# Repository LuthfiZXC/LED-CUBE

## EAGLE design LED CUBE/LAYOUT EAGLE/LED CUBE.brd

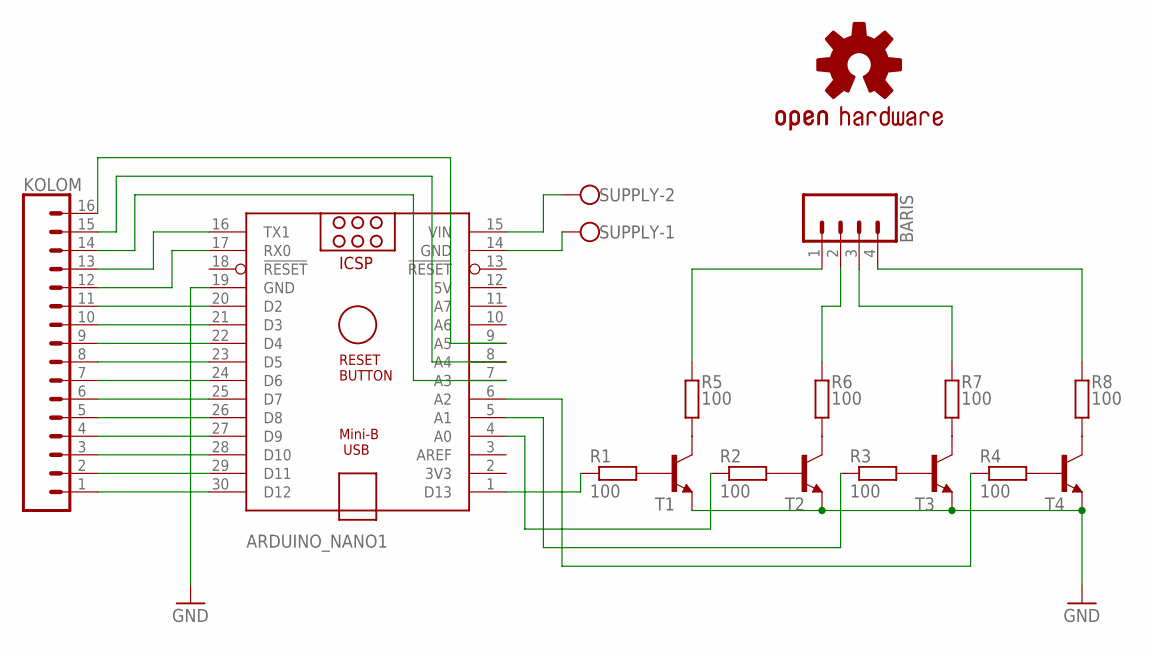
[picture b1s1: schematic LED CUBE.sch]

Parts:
ARDUINO_NANO1: ARDUINO_NANO
BARIS: CONN_04LONGPADS; 1X04_LONGPADS
KOLOM: CONN_16LONGPADS; 1X16_LONGPADS
LOGO2: OSHW-LOGOL-COPPER; OSHW-LOGO-L_COPPER
R1, R2, R3, R4: 100; 0411/15
R5, R6, R7, R8: 100; 0309/10
SUPPLY: W237-102
T1, T2, T3, T4: -NPN-TO92-EBC; TO92-EBC

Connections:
5V: ARDUINO_NANO1.12 (5V)
GND: ARDUINO_NANO1.19 (GND), T1.E, T2.E, T3.E, T4.E
unnamed: ARDUINO_NANO1.30 (D12), KOLOM.1
unnamed: ARDUINO_NANO1.29 (D11), KOLOM.2
unnamed: ARDUINO_NANO1.28 (D10), KOLOM.3
unnamed: ARDUINO_NANO1.27 (D9), KOLOM.4
unnamed: ARDUINO_NANO1.26 (D8), KOLOM.5
unnamed: ARDUINO_NANO1.25 (D7), KOLOM.6
unnamed: ARDUINO_NANO1.24 (D6), KOLOM.7
unnamed: ARDUINO_NANO1.23 (D5), KOLOM.8
unnamed: ARDUINO_NANO1.22 (D4), KOLOM.9
unnamed: ARDUINO_NANO1.21 (D3), KOLOM.10
unnamed: ARDUINO_NANO1.20 (D2), KOLOM.11
unnamed: ARDUINO_NANO1.17 (RX0), KOLOM.12
unnamed: ARDUINO_NANO1.16 (TX1), KOLOM.13
unnamed: ARDUINO_NANO1.7 (A3), KOLOM.14
unnamed: ARDUINO_NANO1.14 (GND), SUPPLY.1
unnamed: ARDUINO_NANO1.8 (A4), KOLOM.15
unnamed: ARDUINO_NANO1.9 (A5), KOLOM.16
unnamed: R1.2, T1.B
unnamed: R2.2, T2.B
unnamed: R3.2, T3.B
unnamed: R4.2, T4.B
unnamed: ARDUINO_NANO1.1 (D13), R1.1
unnamed: ARDUINO_NANO1.4 (A0), R2.1
unnamed: ARDUINO_NANO1.5 (A1), R3.1
unnamed: ARDUINO_NANO1.6 (A2), R4.1
unnamed: R5.1, T1.C
unnamed: R6.1, T2.C
unnamed: R7.1, T3.C
unnamed: R8.1, T4.C
unnamed: BARIS.1, R5.2
unnamed: BARIS.2, R6.2
unnamed: BARIS.3, R7.2
unnamed: BARIS.4, R8.2
unnamed: ARDUINO_NANO1.15 (VIN), SUPPLY.2

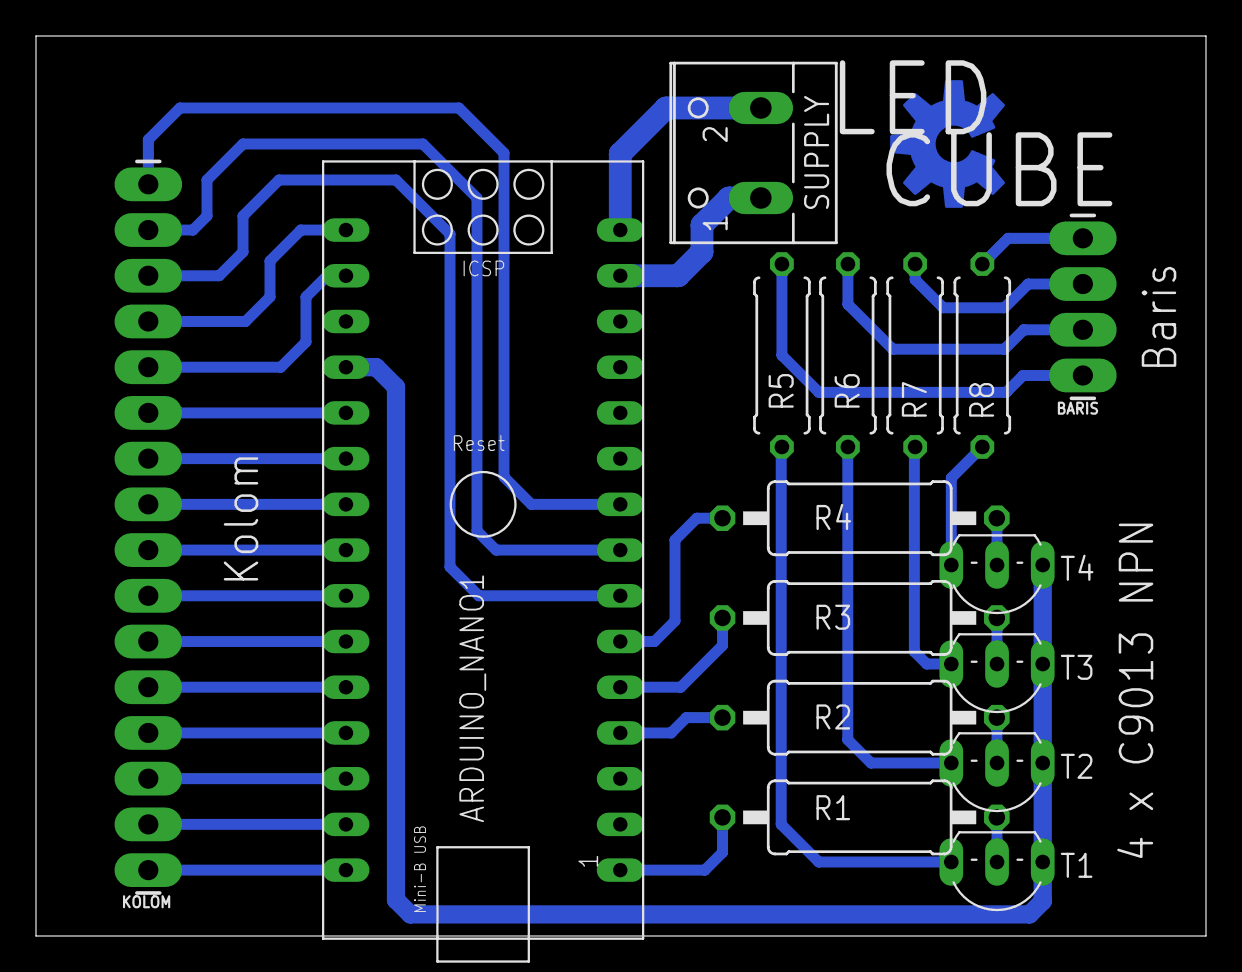
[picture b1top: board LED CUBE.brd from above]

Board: 2 copper layers, 65.0 x 50.0 mm, 17 parts (1 on the bottom side), 35 nets.

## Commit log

2020-07-14 Add files via upload
    PICT LED CUBE

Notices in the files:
parts and their libraries:
SparkFun-Connectors: Licensing: Creative Commons ShareAlike 4.0 International - https://creativecommons.org/licenses/by-sa/4.0
